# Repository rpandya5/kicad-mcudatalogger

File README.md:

# mcudatalogger

This project contains the KiCad files for a PCB for an MCU datalogger, as part of the "[KiCad Like a Pro 3e]([url](https://www.udemy.com/course/kicad-like-a-pro-3e))" course on Udemy. The datalogger incorporates a built-in 512K EEPROM and a real-time clock to facilitate precise data collection and storage.

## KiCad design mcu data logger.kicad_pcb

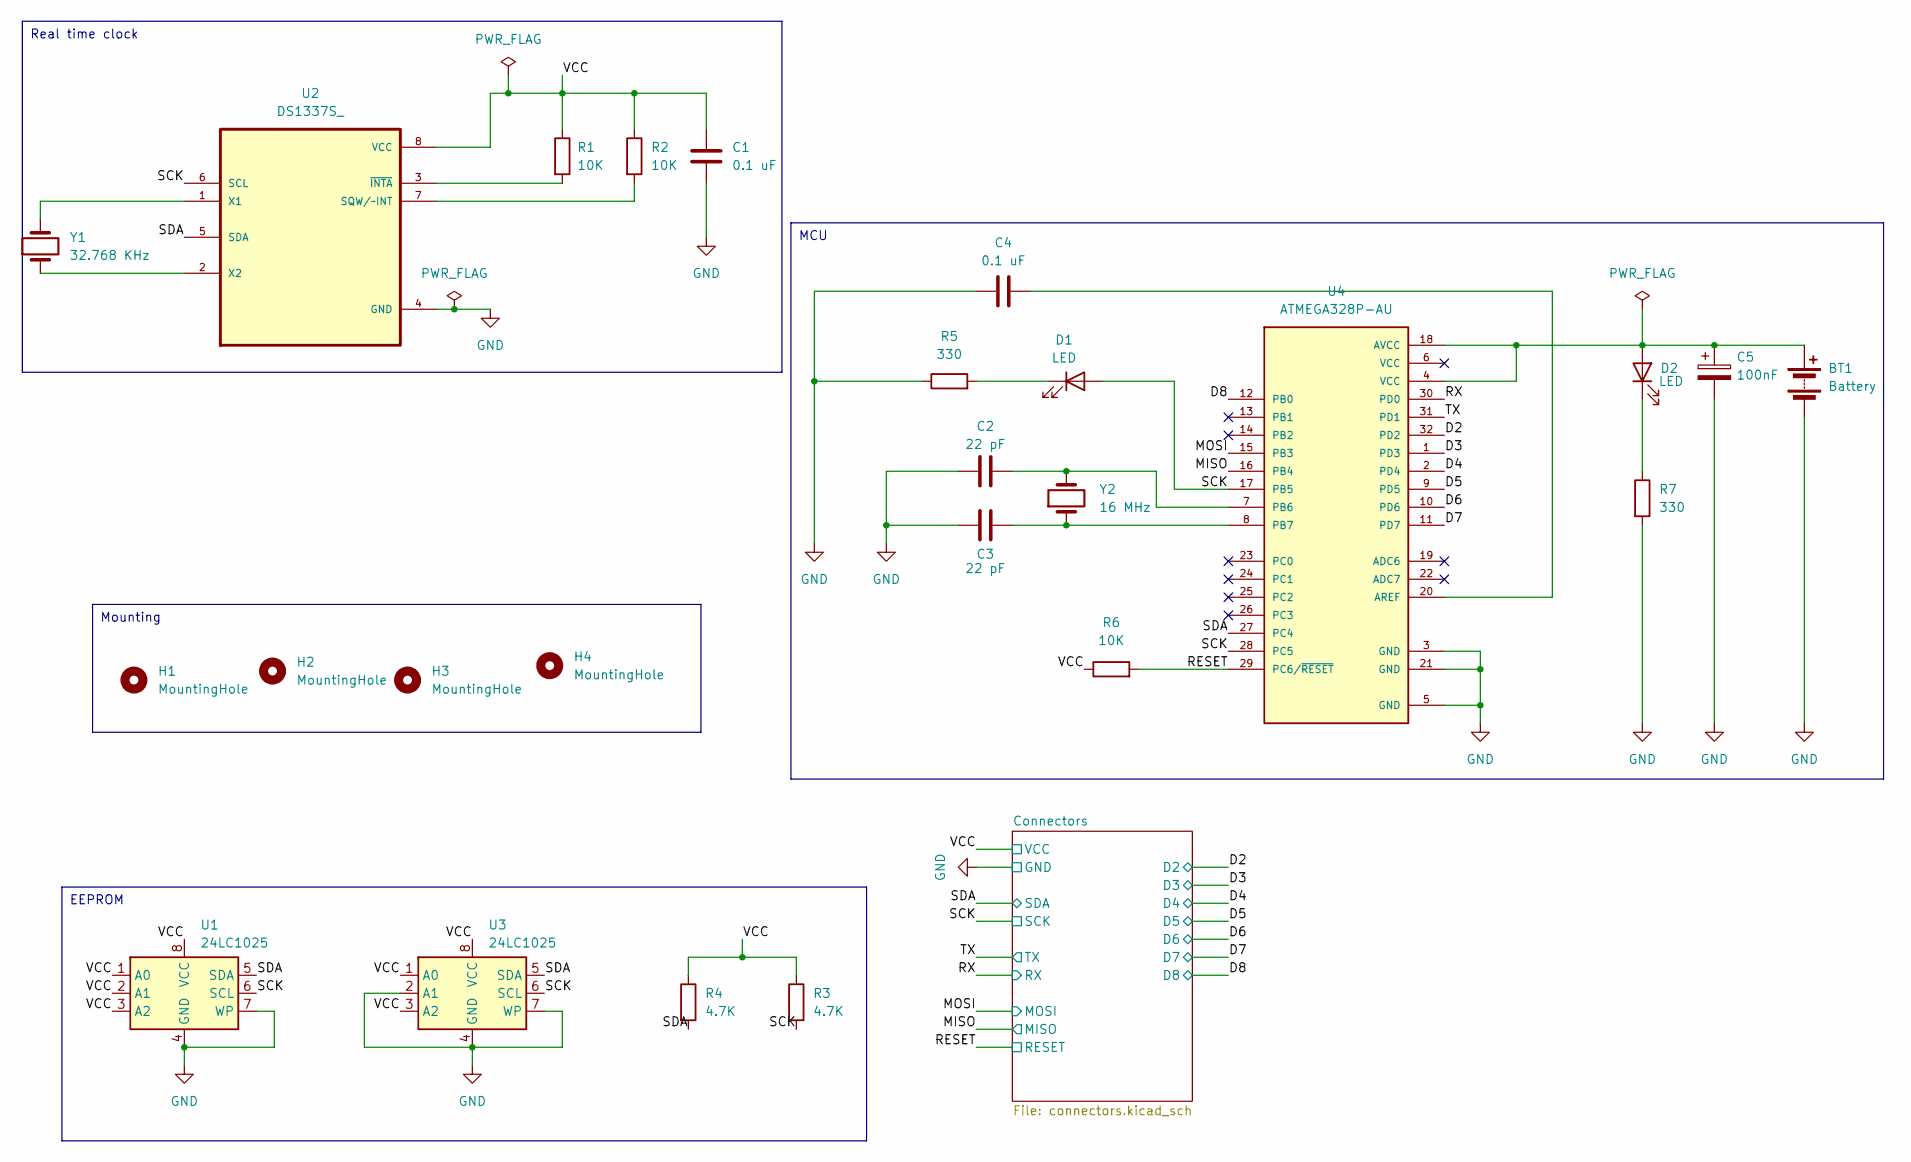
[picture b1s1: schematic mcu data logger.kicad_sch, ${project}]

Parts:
BT1: Battery; PinHeader_1x02_P2.54mm_Vertical
C1, C4: 0.1 uF; C_0805_2012Metric
C2, C3: 22 pF; C_0805_2012Metric
C5: 100nF; C_0805_2012Metric
D1, D2: LED; LED_0805_2012Metric
H1, H2, H3, H4: MountingHole; MountingHole_2.1mm
R1, R2, R6: 10K; R_0805_2012Metric
R3, R4: 4.7K; R_0805_2012Metric
R5, R7: 330; R_0805_2012Metric
U1, U3: 24LC1025; SOIC-8_5.23x5.23mm_P1.27mm
U2: DS1337S_; SOIC127P600X175-8N
U4: ATMEGA328P-AU; QFP80P900X900X120-32N; PARTREV 8271A
Y1: 32.768 KHz; Crystal_SMD_5032-2Pin_5.0x3.2mm_HandSoldering
Y2: 16 MHz; Crystal_SMD_5032-2Pin_5.0x3.2mm_HandSoldering

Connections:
/D2: U4.32 (PD2); also elsewhere on the board
/D3: U4.1 (PD3); also elsewhere on the board
/D4: U4.2 (PD4); also elsewhere on the board
/D5: U4.9 (PD5); also elsewhere on the board
/D6: U4.10 (PD6); also elsewhere on the board
/D7: U4.11 (PD7); also elsewhere on the board
/D8: U4.12 (PB0); also elsewhere on the board
/MISO: U4.16 (PB4); also elsewhere on the board
/MOSI: U4.15 (PB3); also elsewhere on the board
/RESET: R6.2, U4.29 (PC6/~RESET); also elsewhere on the board
/RX: U4.30 (PD0); also elsewhere on the board
/SCK: D1.2 (A), R3.2, U1.6 (SCL), U2.6 (SCL), U3.6 (SCL), U4.17 (PB5), U4.28 (PC5); also elsewhere on the board
/SDA: R4.2, U1.5 (SDA), U2.5 (SDA), U3.5 (SDA), U4.27 (PC4); also elsewhere on the board
/TX: U4.31 (PD1); also elsewhere on the board
/VCC: C1.1, R1.1, R2.1, R3.1, R4.1, R6.1, U1.1 (A0), U1.2 (A1), U1.3 (A2), U1.8 (VCC), U2.8 (VCC), U3.1 (A0), U3.3 (A2), U3.8 (VCC); also elsewhere on the board
GND: BT1.2 (-), C1.2, C2.2, C3.2, C4.1, C5.2, R5.1, R7.2, U1.4 (GND), U1.7 (WP), U2.4 (GND), U3.2 (A1), U3.4 (GND), U3.7 (WP), U4.3 (GND), U4.5 (GND), U4.21 (GND); also elsewhere on the board
unnamed: BT1.1 (+), C5.1, D2.2 (A), U4.4 (VCC), U4.18 (AVCC)
unnamed: D1.1 (K), R5.2
unnamed: D2.1 (K), R7.1
unnamed: R2.2, U2.7 (SQW/~INT)
unnamed: U2.1 (X1), Y1.2
unnamed: U2.2 (X2), Y1.1
unnamed: R1.2, U2.3 (~INTA)
unnamed: C4.2, U4.20 (AREF)
unnamed: C2.1, U4.7 (PB6), Y2.2
unnamed: C3.1, U4.8 (PB7), Y2.1

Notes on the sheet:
Mounting
MCU
Real time clock
EEPROM

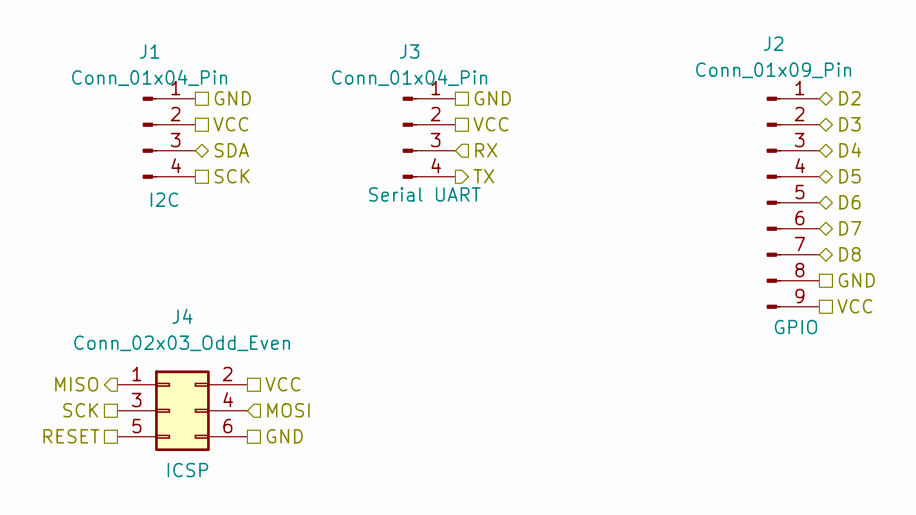
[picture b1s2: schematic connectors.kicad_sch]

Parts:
J1, J3: Conn_01x04_Pin; PinHeader_1x04_P2.54mm_Vertical
J2: Conn_01x09_Pin; PinHeader_1x09_P2.54mm_Vertical
J4: Conn_02x03_Odd_Even; PinHeader_2x03_P2.54mm_Vertical

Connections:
/D2: J2.1; also elsewhere on the board
/D3: J2.2; also elsewhere on the board
/D4: J2.3; also elsewhere on the board
/D5: J2.4; also elsewhere on the board
/D6: J2.5; also elsewhere on the board
/D7: J2.6; also elsewhere on the board
/D8: J2.7; also elsewhere on the board
/MISO: J4.1; also elsewhere on the board
/MOSI: J4.4; also elsewhere on the board
/RESET: J4.5; also elsewhere on the board
/RX: J3.3; also elsewhere on the board
/SCK: J1.4, J4.3; also elsewhere on the board
/SDA: J1.3; also elsewhere on the board
/TX: J3.4; also elsewhere on the board
/VCC: J1.2, J2.9, J3.2, J4.2; also elsewhere on the board
GND: J1.1, J2.8, J3.1, J4.6; also elsewhere on the board

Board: 2 copper layers, 29 parts (0 on the bottom side), 26 nets, no tracks yet.

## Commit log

2024-05-12 completed project
2024-05-12 Update .gitignore and untrack specified files
2024-05-12 completed silkscreen printing for board
2024-05-12 completed wiring
2024-05-12 added all symbols onto schematic
2024-05-12 changed location of symbols
2024-05-12 Added component values
2024-05-12 allocated gnd and vcc to power net class
2024-05-12 Add .gitignore file
2024-05-12 Setup of EEschema for new project
2024-05-12 completed symbol footprint associations
2024-05-12 setup pcbnew
2024-05-12 added comments
2024-05-12 completed wiring in the schemeatic
2024-05-12 completed routing
2024-05-12 First commit of new project.
2024-05-12 finished schematic
2024-05-12 files
2024-05-12 Completed wiring of main sheet
2024-05-12 completed board layout
